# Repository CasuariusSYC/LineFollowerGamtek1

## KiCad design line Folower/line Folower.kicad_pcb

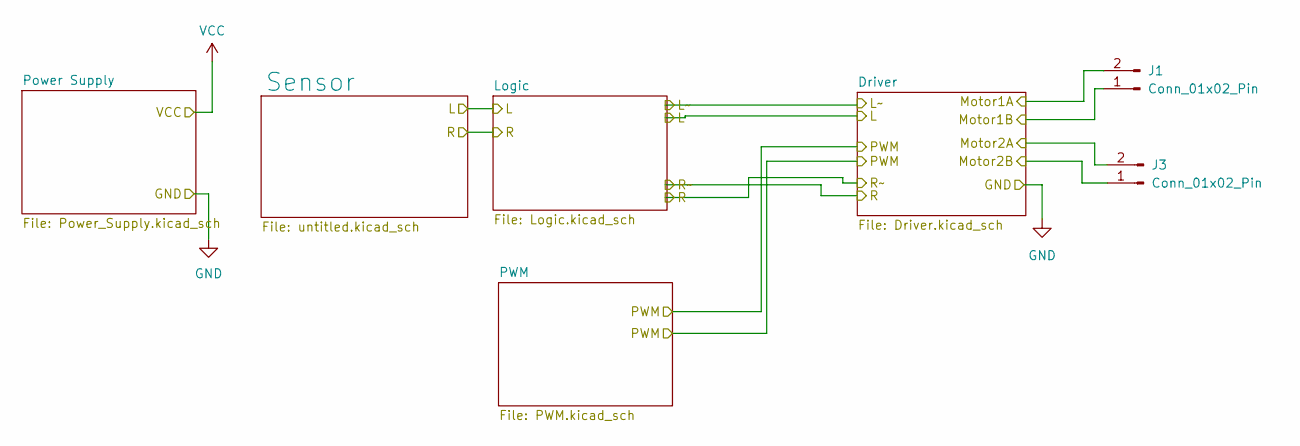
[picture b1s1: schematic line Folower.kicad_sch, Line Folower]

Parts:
J1, J3: Conn_01x02_Pin; TerminalBlock_Phoenix_MKDS-1,5-2-5.08_1x02_P5.08mm_Horizont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

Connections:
Motor1A: J1.2; also elsewhere on the board
Motor1B: J1.1; also elsewhere on the board
Motor2A: J3.2; also elsewhere on the board
Motor2B: J3.1; also elsewhere on the board

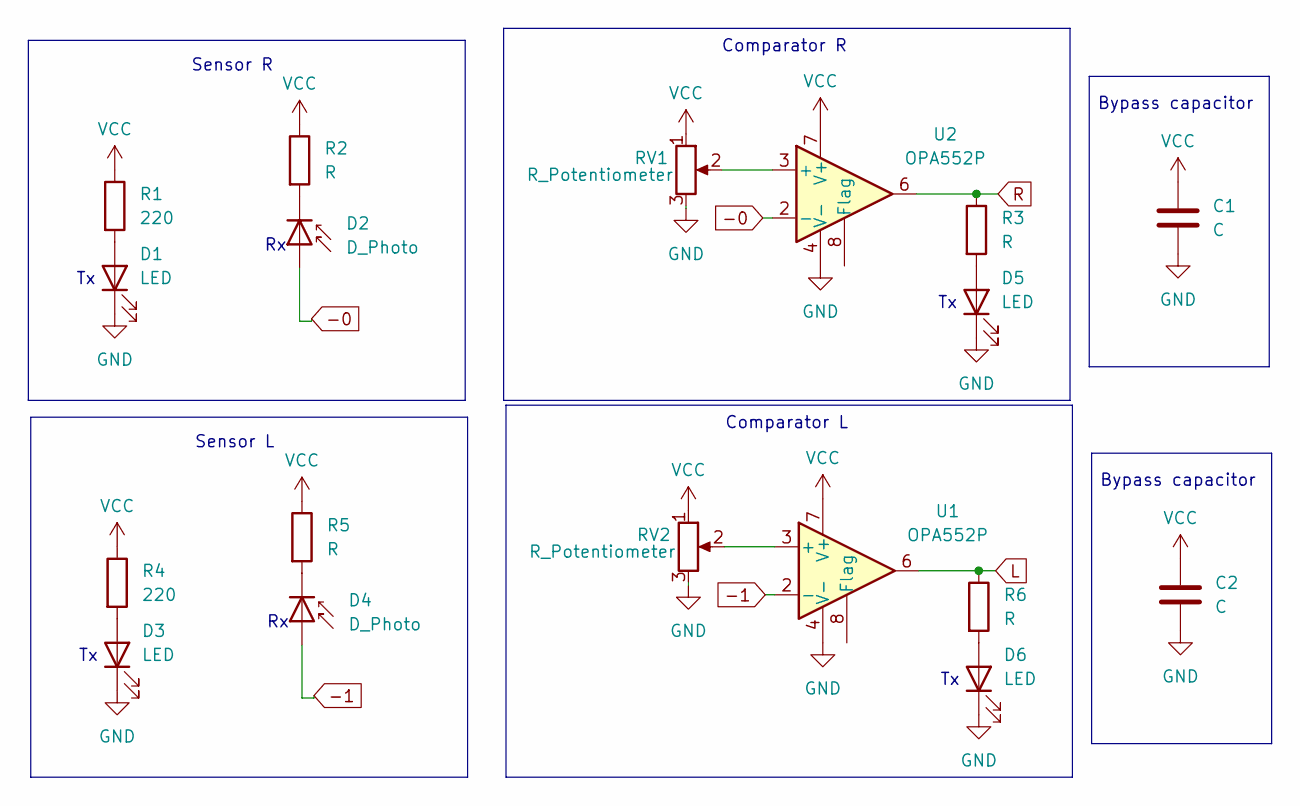
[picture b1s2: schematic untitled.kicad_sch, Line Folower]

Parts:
C1, C2: C; C_Disc_D5.0mm_W2.5mm_P5.00mm
D1, D3, D5, D6: LED; LED_D5.0mm
D2, D4: D_Photo; LED_D5.0mm
R1, R4: 220; R_Axial_DIN0207_L6.3mm_D2.5mm_P7.62mm_Horizontal
R2, R3, R5, R6: R; R_Axial_DIN0207_L6.3mm_D2.5mm_P7.62mm_Horizontal
RV1, RV2: R_Potentiometer; Potentiometer_Bourns_3296W_Vertical
U1, U2: OPA552P; DIP-8_W7.62mm

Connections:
-0: D2.2 (A), U2.2 (-)
-1: D4.2 (A), U1.2 (-)
GND: C1.2, C2.2, D1.1 (K), D3.1 (K), D5.1 (K), D6.1 (K), RV1.3, RV2.3, U1.4 (V-), U2.4 (V-); also elsewhere on the board
L: R6.1, U1.6; also elsewhere on the board
unnamed: D1.2 (A), R1.2
unnamed: D2.1 (K), R2.2
unnamed: D3.2 (A), R4.2
unnamed: D4.1 (K), R5.2
unnamed: D5.2 (A), R3.2
unnamed: D6.2 (A), R6.2
unnamed: RV2.2, U1.3 (+)
unnamed: RV1.2, U2.3 (+)
R: R3.1, U2.6; also elsewhere on the board
VCC: C1.1, C2.1, R1.1, R2.1, R4.1, R5.1, RV1.1, RV2.1, U1.7 (V+), U2.7 (V+); also elsewhere on the board

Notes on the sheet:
Comparator R
Bypass capacitor
Sensor L
Comparator L
Sensor R

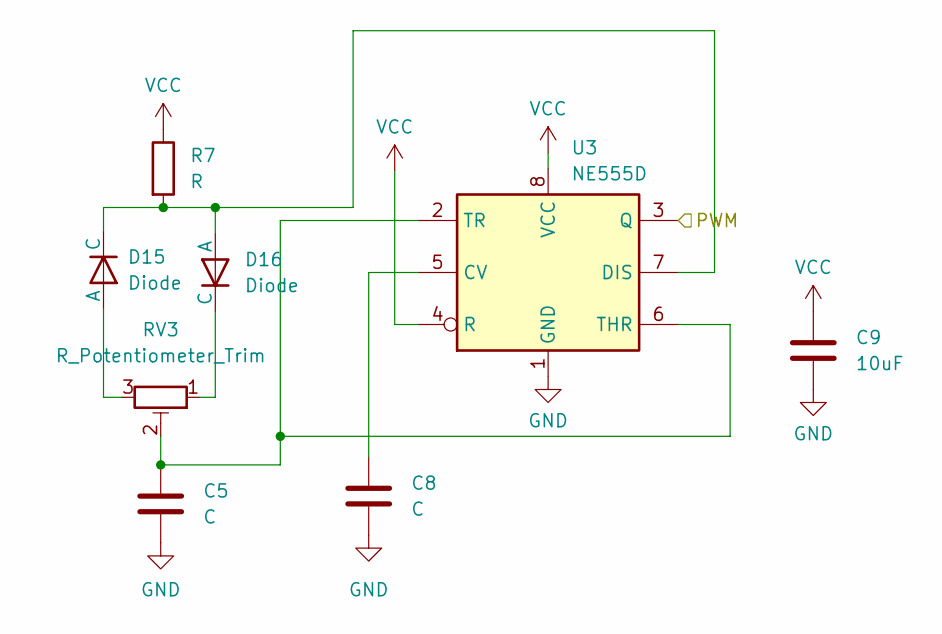
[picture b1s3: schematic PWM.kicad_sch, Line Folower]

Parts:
C5: C; CP_Radial_D6.3mm_P2.50mm
C8: C; C_Disc_D5.0mm_W2.5mm_P5.00mm
C9: 10uF; C_Disc_D5.0mm_W2.5mm_P5.00mm
D15, D16: Diode; D_DO-35_SOD27_P7.62mm_Horizontal
R7: R; R_Axial_DIN0207_L6.3mm_D2.5mm_P7.62mm_Horizontal
RV3: R_Potentiometer_Trim; Potentiometer_Bourns_3296W_Vertical
U3: NE555D; DIP-8_W7.62mm

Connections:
GND: C5.2, C8.2, C9.2, U3.1 (GND); also elsewhere on the board
unnamed: D15.1 (A), RV3.3
unnamed: D15.2 (C), D16.1 (A), R7.2, U3.7 (DIS)
unnamed: D16.2 (C), RV3.1
unnamed: C8.1, U3.5 (CV)
unnamed: C5.1, RV3.2, U3.2 (TR), U3.6 (THR)
PWM: U3.3 (Q); also elsewhere on the board
VCC: C9.1, R7.1, U3.4 (R), U3.8 (VCC); also elsewhere on the board

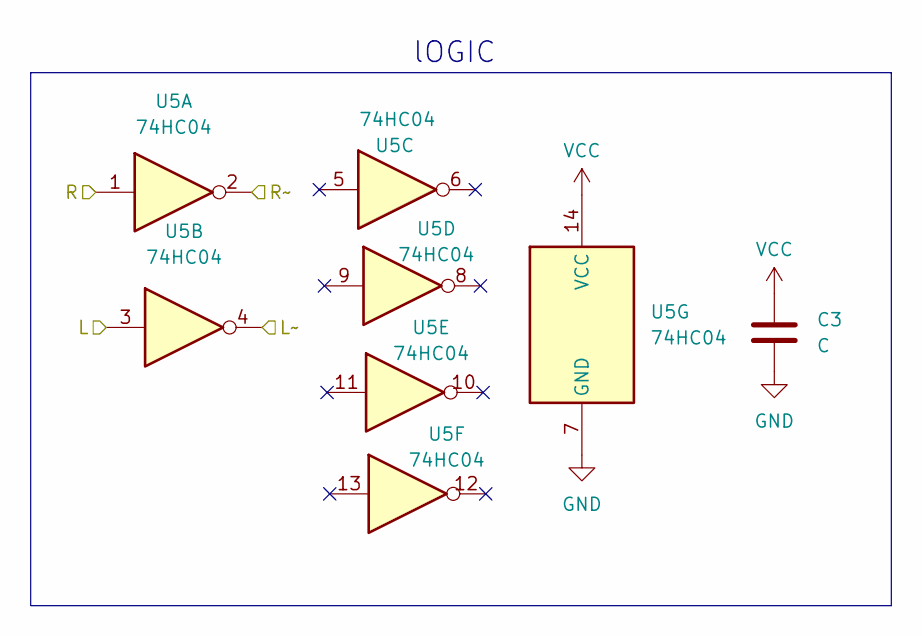
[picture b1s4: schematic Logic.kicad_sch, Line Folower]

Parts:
C3: C; C_Disc_D5.0mm_W2.5mm_P5.00mm
U5: 74HC04; DIP-14_W7.62mm

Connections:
GND: C3.2, U5.7 (GND); also elsewhere on the board
L: U5.3; also elsewhere on the board
L~: U5.4; also elsewhere on the board
R: U5.1; also elsewhere on the board
R~: U5.2; also elsewhere on the board
VCC: C3.1, U5.14 (VCC); also elsewhere on the board

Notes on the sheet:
lOGIC

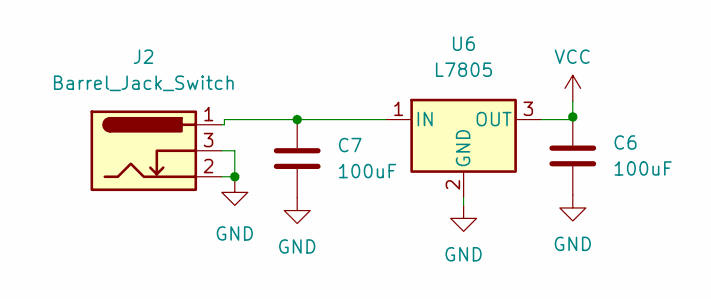
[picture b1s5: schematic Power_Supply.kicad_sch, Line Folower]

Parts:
C6, C7: 100uF; CP_Radial_D6.3mm_P2.50mm
J2: Barrel_Jack_Switch; TerminalBlock_Phoenix_MKDS-1,5-2-5.08_1x02_P5.08mm_Horizont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
U6: L7805; TO-220-3_Vertical

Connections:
GND: C6.2, C7.2, J2.2, J2.3, U6.2 (GND); also elsewhere on the board
unnamed: C7.1, J2.1, U6.1 (IN)
VCC: C6.1, U6.3 (OUT); also elsewhere on the board

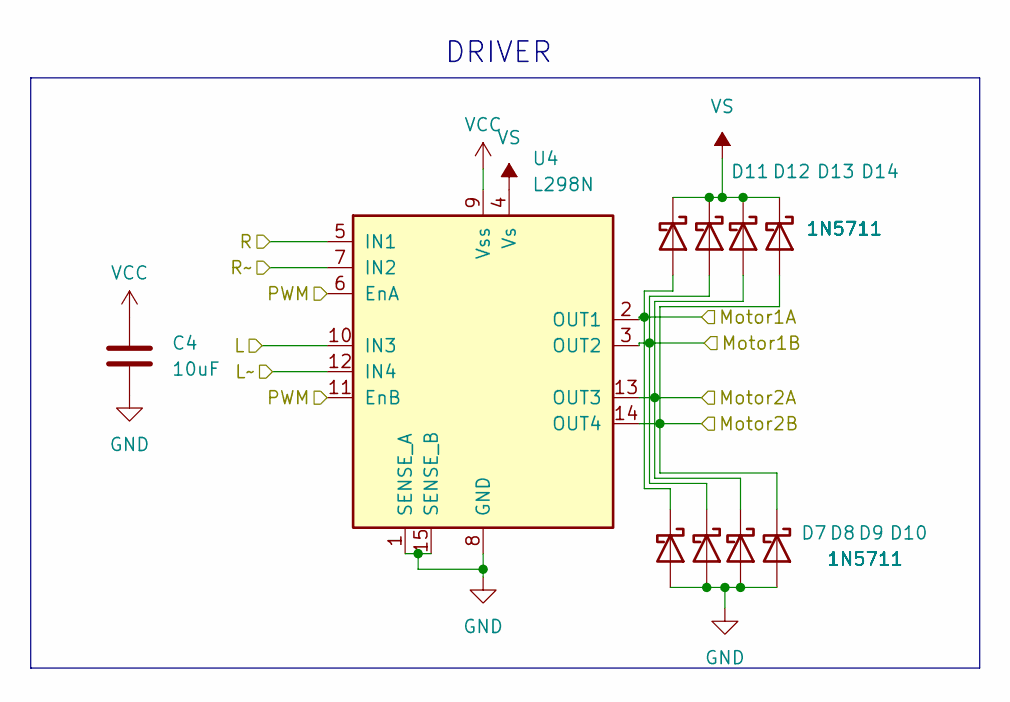
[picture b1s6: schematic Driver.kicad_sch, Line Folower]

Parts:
C4: 10uF; C_Disc_D5.0mm_W2.5mm_P5.00mm
D7, D8, D9, D10, D11, D12, D13, D14: 1N5711; D_DO-41_SOD81_P10.16mm_Horizontal
U4: L298N; TO-220F-15_P2.54x5.08mm_StaggerOdd_Lead5.08mm_Vertical

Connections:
GND: C4.2, D7.2 (A), D8.2 (A), D9.2 (A), D10.2 (A), U4.1 (SENSE_A), U4.8 (GND), U4.15 (SENSE_B); also elsewhere on the board
L: U4.10 (IN3); also elsewhere on the board
L~: U4.12 (IN4); also elsewhere on the board
Motor1A: D7.1 (K), D11.2 (A), U4.2 (OUT1); also elsewhere on the board
Motor1B: D8.1 (K), D12.2 (A), U4.3 (OUT2); also elsewhere on the board
Motor2A: D9.1 (K), D13.2 (A), U4.13 (OUT3); also elsewhere on the board
Motor2B: D10.1 (K), D14.2 (A), U4.14 (OUT4); also elsewhere on the board
PWM: U4.6 (EnA), U4.11 (EnB); also elsewhere on the board
R: U4.5 (IN1); also elsewhere on the board
R~: U4.7 (IN2); also elsewhere on the board
VCC: C4.1, U4.9 (Vss); also elsewhere on the board
VS: D11.1 (K), D12.1 (K), D13.1 (K), D14.1 (K), U4.4 (Vs)

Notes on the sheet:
DRIVER

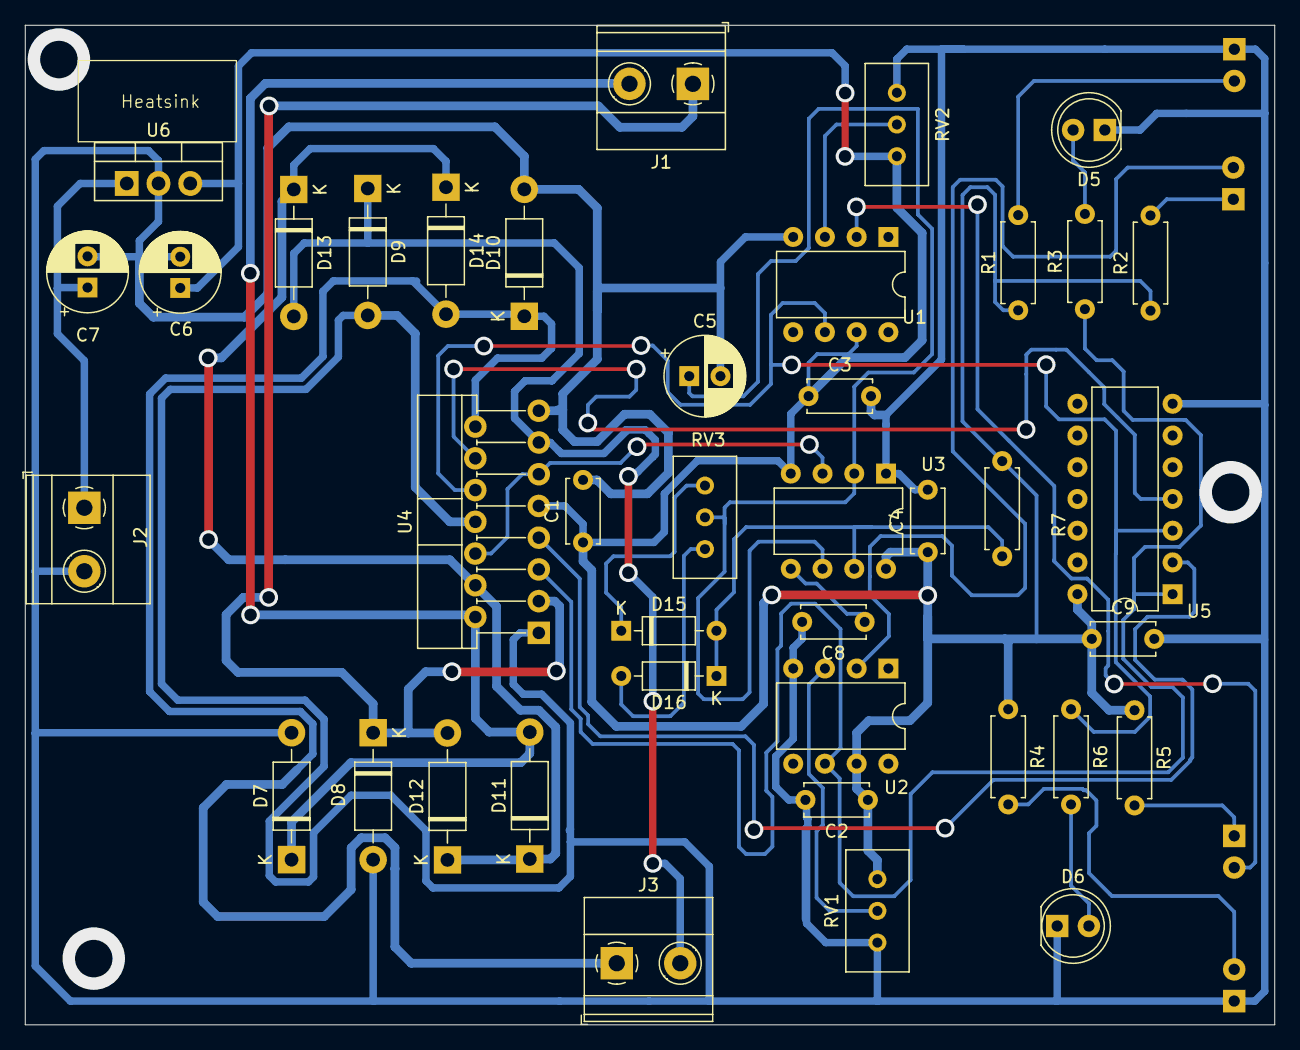
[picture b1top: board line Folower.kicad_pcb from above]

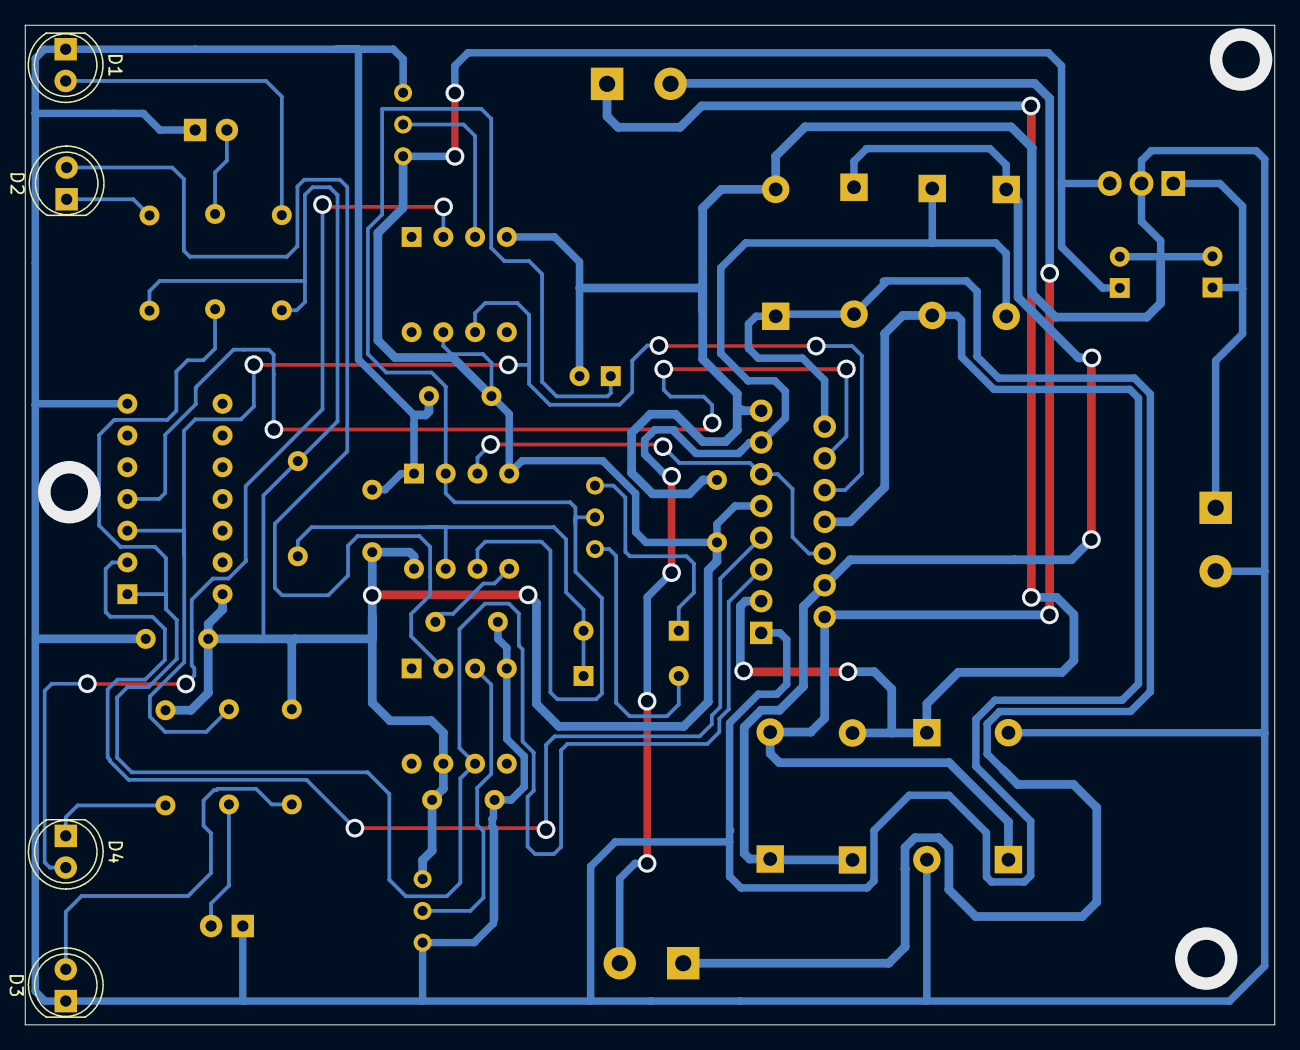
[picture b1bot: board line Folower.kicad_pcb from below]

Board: 2 copper layers, 100.0 x 80.0 mm, 44 parts (4 on the bottom side), 28 nets.
